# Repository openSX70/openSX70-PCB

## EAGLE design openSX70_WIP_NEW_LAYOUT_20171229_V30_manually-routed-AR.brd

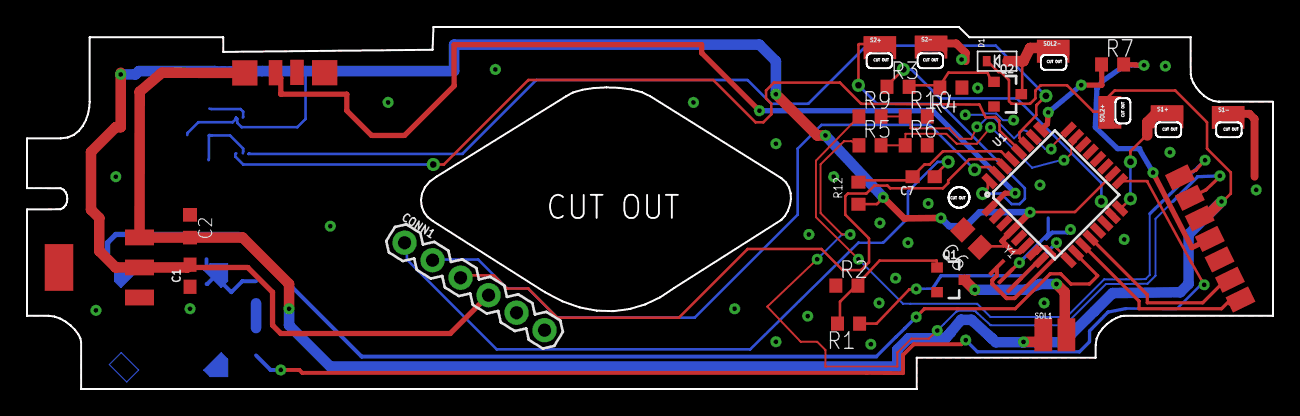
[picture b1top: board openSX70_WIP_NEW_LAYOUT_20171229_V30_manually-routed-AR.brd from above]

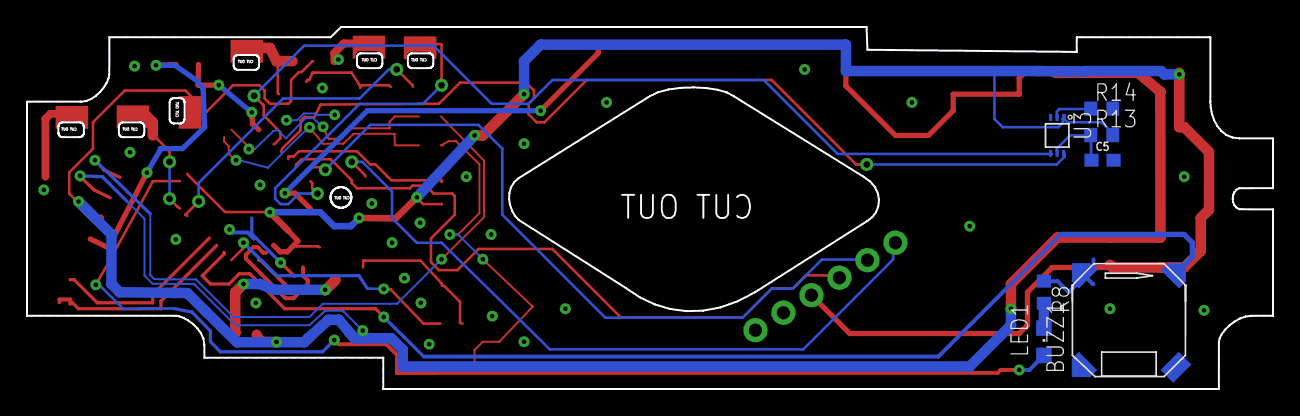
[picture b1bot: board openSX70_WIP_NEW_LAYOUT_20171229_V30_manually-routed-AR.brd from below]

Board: 2 copper layers, 95.9 x 27.9 mm, 37 parts (7 on the bottom side), 33 nets.

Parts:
BUZZ1: CSET8-5G; CSET8-5G_PACKAGE
C1, C5: 10uF; 0603
C2: 100nF; C0603K
C6: 100nF; C0805
C7: 0.1uF; 0603
CONN1: FTDI HEADER; 1X06
D1: SOD-523
LD11173.3V: LD1117 3.3V; SOT223
LED1: CHIPLED_0805
Q1, Q2: 5.8A/30V/35mΩ; SOT23-3
R1, R3, R7: 100R; R0603
R2, R4: 100K; R0603
R5, R9: 12K; R0603
R6, R10: 15K; R0603
R8: 470R; R0603
R12: 10K; R0603
R13: 1K; R0603
R14: 4K7; R0603
S1+, S1-, S2+, S2-: SX70_S-PAD; SX70-S-PAD
SOL1: SX70-SOLENOID1-2PADS; SX70-SOLENOID1-2
SOL2+, SOL2-: SX70_S-PAD; SX70-S-PAD
U1: ATMEGA328P_TQFP; TQFP32-08
U3: BH1750FVI-TR; SOTFL50P300X75-6N
U$1: SX70-7-PAD
U$2: FFA; FFA-PAD-PACKAGE
Y1: CSTCE16M0V53-R0; CFP95P160X100-3N

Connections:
3.3V: C1.2, C6.1, CONN1.4, LD11173.3V.2, R12.2, R13.2, U1.4, U1.6, U1.18, U3.1
6V: C2.2, D1.K, LD11173.3V.3, SOL1.SOL1+, SOL2+.P$1, U$1.VCC-6V, U$2.F+
BUZZER: BUZZ1.+, U1.10
DTR: C7.1, CONN1.1
FF: U1.1, U$2.FF
GND: BUZZ1.GND-, C1.1, C2.1, C5.2, C6.2, CONN1.6, LD11173.3V.1, Q1.2, Q2.2, R2.1, R4.1, R6.2, R8.1, R10.2, R14.2, S1-.P$1, S2-.P$1, U1.3, U1.5, U1.21, U3.3, U$1.GND, U$2.F-, Y1.GND
LED: LED1.A, U1.17
MOTOR+: R7.1, U1.25
MOTOR-HEADER: R7.2, U$1.MOTOR+
unnamed: Q1.1, R1.2, R2.2
unnamed: C5.1, R13.1, U3.5
unnamed: Q2.1, R3.2, R4.2
unnamed: U1.7, Y1.IN
unnamed: LED1.C, R8.2
unnamed: U1.8, Y1.OUT
unnamed: C7.2, R12.1, U1.29
unnamed: R14.1, U3.2
RXD: CONN1.3, U1.30
S1: S1+.P$1, U1.16
S2: S2+.P$1, U1.32
S3: U1.12, U$1.S3
S5: U1.11, U$1.S5
S8@3.3V: R9.2, R10.1, U1.24
S8@6V: R9.1, U$1.S8
S9@3.3V: R5.2, R6.1, U1.23
S9@6V: R5.1, U$1.S9
SCL: U1.28, U3.6
SDA: U1.27, U3.4
SOL1: R1.1, U1.9
SOL1-: Q1.3, SOL1.SOL1-
SOL2: R3.1, U1.15
SOL2-: D1.A, Q2.3, SOL2-.P$1
TXD: CONN1.2, U1.31

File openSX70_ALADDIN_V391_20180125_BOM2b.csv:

Qty,Value,Device,Package,Parts,Description,,
1,,LEDCHIPLED_0805,CHIPLED_0805,LED1,LED,,
1,0.1uF,0.1UF-0603-25V-(+80/-20%),0603,C7,0.1µF ceramic capacitors,,
2,100K,R-US_R0603,R0603,R2, R4,RESISTOR, American symbol,,
3,100R,R-US_R0603,R0603,R1, R3, R7,RESISTOR, American symbol,,
1,100nF,C-EUC0603,C0603,C6,CAPACITOR, European symbol,,
1,100nF,C-EUC0603K,C0603K,C2,CAPACITOR, European symbol,,
3,10K,R-US_R0603,R0603,R6, R10, R12,RESISTOR, American symbol,,
2,10uF,10UF-0603-6.3V-20%,0603,C1, C5,10.0µF ceramic capacitors,,
2,15K,R-US_R0603,R0603,R5, R9,RESISTOR, American symbol,,
2,1K,R-US_R0603,R0603,R8, R13,RESISTOR, American symbol,,
2,1N4148WSF,DSOD323,SOD323,D1, D2,DIODE,,
1,4K7,R-US_R0603,R0603,R14,RESISTOR, American symbol,,
2,5.8A/30V/35mO,MOSFET-NCH-AO3404A,SOT23-3,Q1, Q2,N-channel MOSFETs,,
1,ATMEGA328P_TQFP,ATMEGA328P_TQFP,TQFP32-08,U1,Popular 328P in QFP,,
1,BH1750FVI-TR,BH1750FVI-TR,SOTFL50P300X75-6N,U3,Light to Digital Ambient Light Sensor Digital O/P 1lux to 65535lux 6-Pin WSOF Embossed T/R,,
1,CSET8-5G,CSET8-5G,CSET8-5G_PACKAGE,BUZZ1,,,
1,CSTCE16M0V53-R0,CSTCE16M0V53-R0,CFP95P160X100-3N,Y1,Ceramic Resonator 16MHz ±0.5% (Tol) ±0.3% (Stability) 15pF 40Ohm 3-Pin CSMD T/R,,
1,FFA,SX70-FFA-PAD,FFA-PAD-PACKAGE,U$2,,,
1,FTDI VCC SELECTOR,JUMPER-SMT_3_1-NC_TRACE_SILK,SMT-JUMPER_3_1-NC_TRACE_SILK,JP1,Normally closed trace jumper (1 of 2 connections),,
1,GND,XF2L-0625-1,XF2L-0625-1,J1,OMRON FPC Connector,,
1,LD1117 2.5V,LD1117-3.3,SOT223,LD11172.5V,,,
5,PTR1TP08R,PTR1TP08R,TP08R,MISO, MOSI, SCK, SCL, SDA,TEST PIN,,

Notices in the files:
parts and their libraries:
SparkFun-Capacitors: Licensing: Creative Commons ShareAlike 4.0 International - https://creativecommons.org/licenses/by-sa/4.0
